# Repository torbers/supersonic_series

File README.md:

# Supersonic Series

Airplane dragon synthesizers

## Spike chord synthesizer
### Instruction card

### MIDI CC implementation
| Controller | Effect |
| --- | --- |
| 70 | Chord shape |
| 71 | Filter resonance |
| 72 | Amp envelope attack |
| 73 | Amp envelope release |
| 74 | Filter frequency |
| 75 | Delay time |
| 76 | Delay feedback |
| 77 | Detune |
| 78 | Oscillator bank spread |

### Building Arduino code
The Arduino IDE is the easiest, most portable way to compile and upload code to Spike. This section assumes no previous knowledge of the Arduino IDE in order to accommodate coders of all experience levels.
#### 1. Install Arduino IDE
Follow [this tutorial](https://docs.arduino.cc/software/ide-v2/tutorials/getting-started/ide-v2-downloading-and-installing/) to install the Arduino IDE 2 on your computer. The environment supports Windows, Mac, and Linux.

#### 2. Clone this repository
Use your preferred method to "clone" (download) this repository to your computer. I like the [github desktop app](https://desktop.github.com/download/), but you can also just download the whole thing as a .zip from the [main page](https://github.com/torbers/supersonic_series).

#### 3. Open the file
Once the IDE has installed, choose `File->Open` and navigate to and open `supersonic_series/spike copy/spike_v2_usb/spike_v2_usb.ino`. **Make sure** `spike_v2_usb.ino` and the other files stay in the `spike_v2_usb` folder or it won't open correctly!

#### 4. Install libraries
You will need to install 3 libraries from the built-in library manager (the book icon on the side of the Arduino window).
- **Mozzi** by Tim Barrass: This is our sound synthesis library
- **USB-MIDI** by lathoub: This library sends and recieves MIDI over USB
- **Adafruit_NeoPixel** by Adafruit: This library controls the built in LED

#### 5. Connect Spike
Connect Spike to your computer via the USB C port. **Make sure your cable is capable of data transmission or "sync," and isn't a power-only cable.**
It will appear in Arduino as `Arduino Zero (Native USB)` at the top of the screen. Make sure the text saying this is bold - if so, you're ready to upload.

#### 6. Compile and upload!
Press the arrow button at the top left of the screen to compile and upload the code.

---
## Licensing
All work is shared under [Creative Commons CC BY-SA 4.0](https://creativecommons.org/licenses/by-sa/4.0/): Anyone is free to share, remix, and commercialize it so long as they attribute the work and release it under this same license agreement. (Attribution text modified from [here](https://fullyautomatedrpg.com/licensing/).)

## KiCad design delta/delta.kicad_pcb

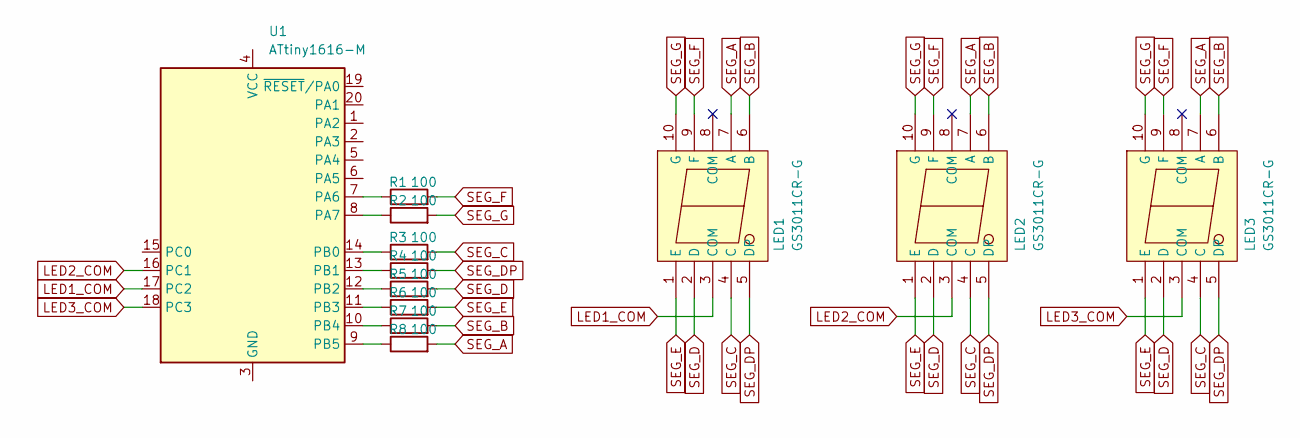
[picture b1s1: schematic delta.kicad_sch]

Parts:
LED1, LED2, LED3: GS3011CR-G; LED-SEG-SMD_10P-L12.0-W7.3-P1.50-BL; MPN GS3011CR-G; LCSC Part C22462656
R1, R2, R3, R4, R5, R6, R7, R8: 100; R_0402_1005Metric
U1: ATtiny1616-M; VQFN-20-1EP_3x3mm_P0.4mm_EP1.7x1.7mm

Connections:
LED1_COM: LED1.3 (COM), U1.17 (PC2)
LED2_COM: LED2.3 (COM), U1.16 (PC1)
LED3_COM: LED3.3 (COM), U1.18 (PC3)
unnamed: U1.3 (GND), U1.21 (GND)
unnamed: R1.1, U1.7 (PA6)
unnamed: R2.1, U1.8 (PA7)
unnamed: R3.1, U1.14 (PB0)
unnamed: R4.1, U1.13 (PB1)
unnamed: R5.1, U1.12 (PB2)
unnamed: R6.1, U1.11 (PB3)
unnamed: R7.1, U1.10 (PB4)
unnamed: R8.1, U1.9 (PB5)
SEG_A: LED1.7 (A), LED2.7 (A), LED3.7 (A), R8.2
SEG_B: LED1.6 (B), LED2.6 (B), LED3.6 (B), R7.2
SEG_C: LED1.4 (C), LED2.4 (C), LED3.4 (C), R3.2
SEG_D: LED1.2 (D), LED2.2 (D), LED3.2 (D), R5.2
SEG_DP: LED1.5 (DP), LED2.5 (DP), LED3.5 (DP), R4.2
SEG_E: LED1.1 (E), LED2.1 (E), LED3.1 (E), R6.2
SEG_F: LED1.9 (F), LED2.9 (F), LED3.9 (F), R1.2
SEG_G: LED1.10 (G), LED2.10 (G), LED3.10 (G), R2.2

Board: 4 copper layers, 12 parts (9 on the bottom side), 20 nets, no tracks yet.

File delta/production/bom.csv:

Designator,Footprint,Quantity,Value,LCSC Part #
"LED1, LED2, LED3",LED-SEG-SMD_10P-L12.0-W7.3-P1.50-BL,3,GS3011CR-G,C22462656
U1,VQFN-20-1EP_3x3mm_P0.4mm_EP1.7x1.7mm,1,ATtiny1616-M,

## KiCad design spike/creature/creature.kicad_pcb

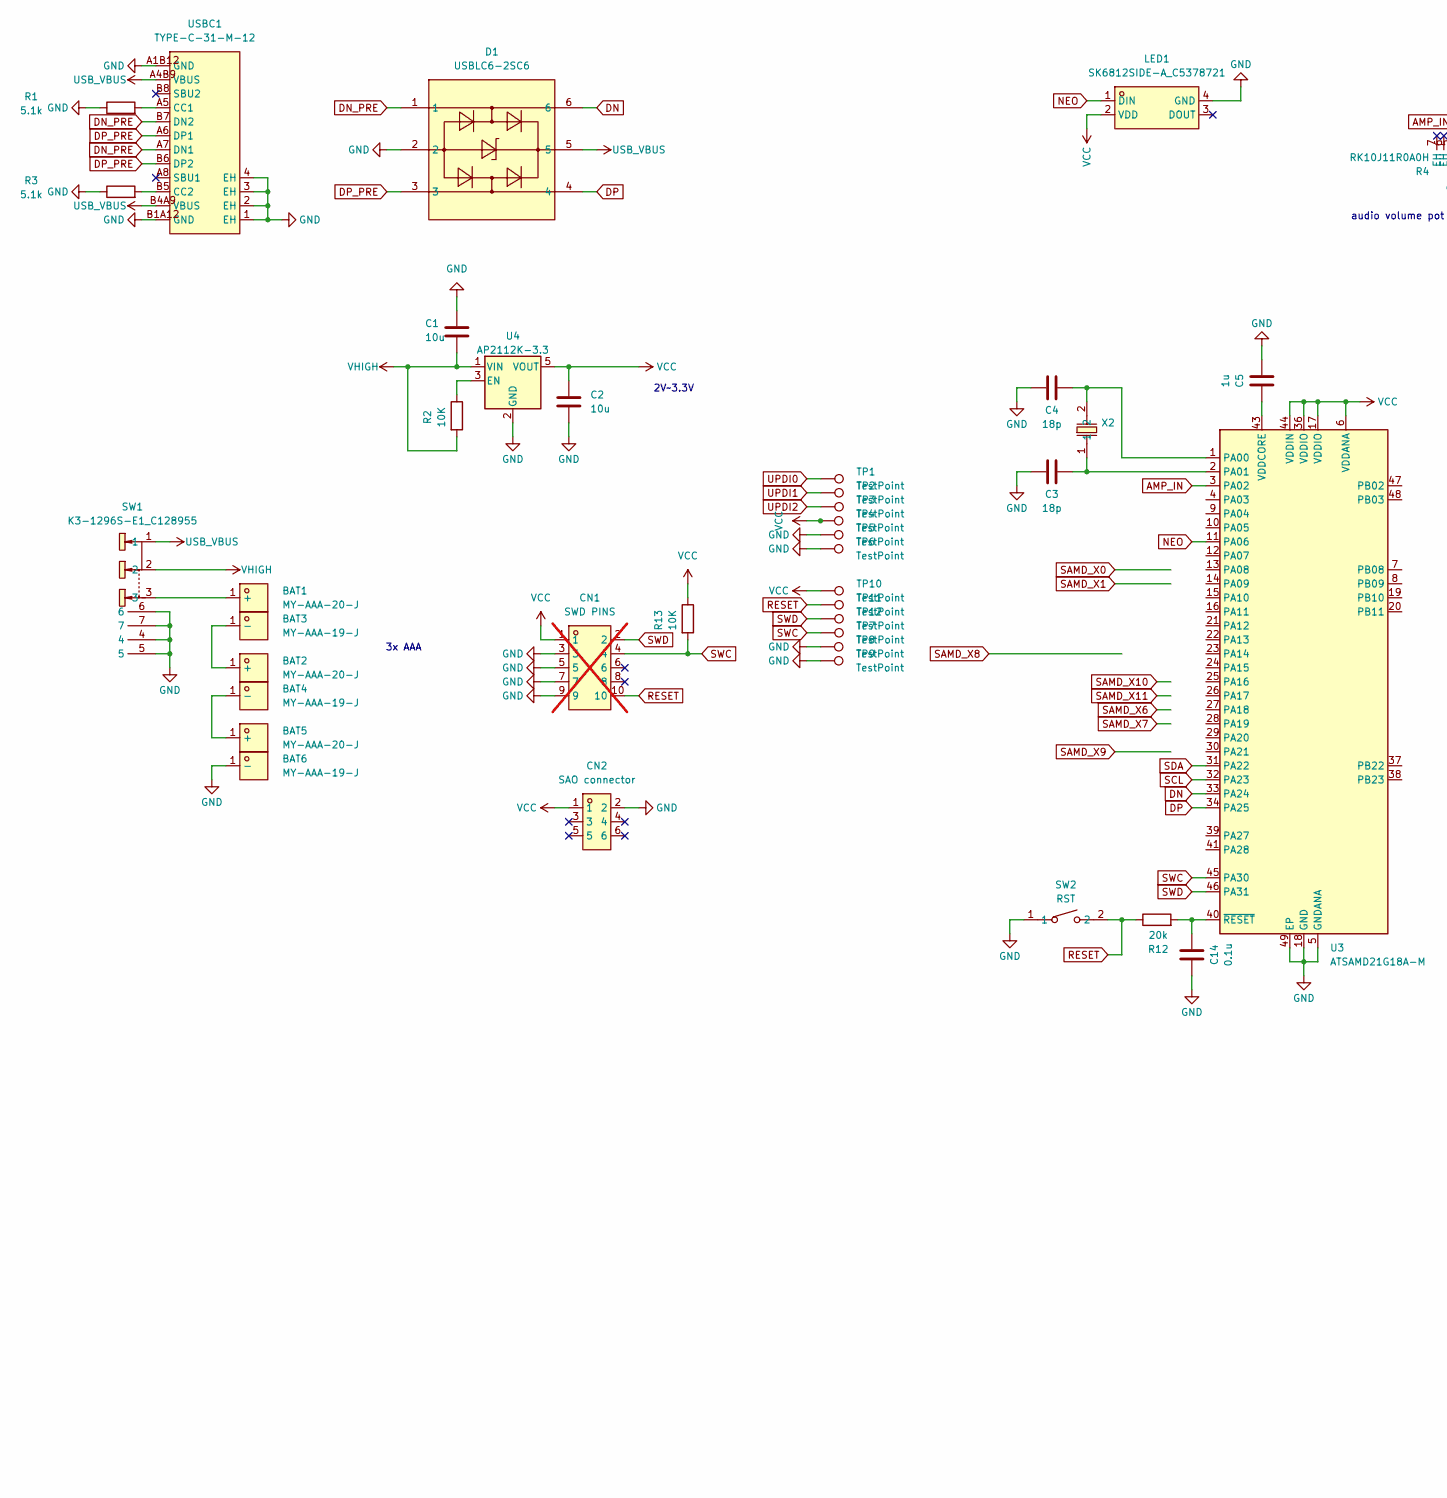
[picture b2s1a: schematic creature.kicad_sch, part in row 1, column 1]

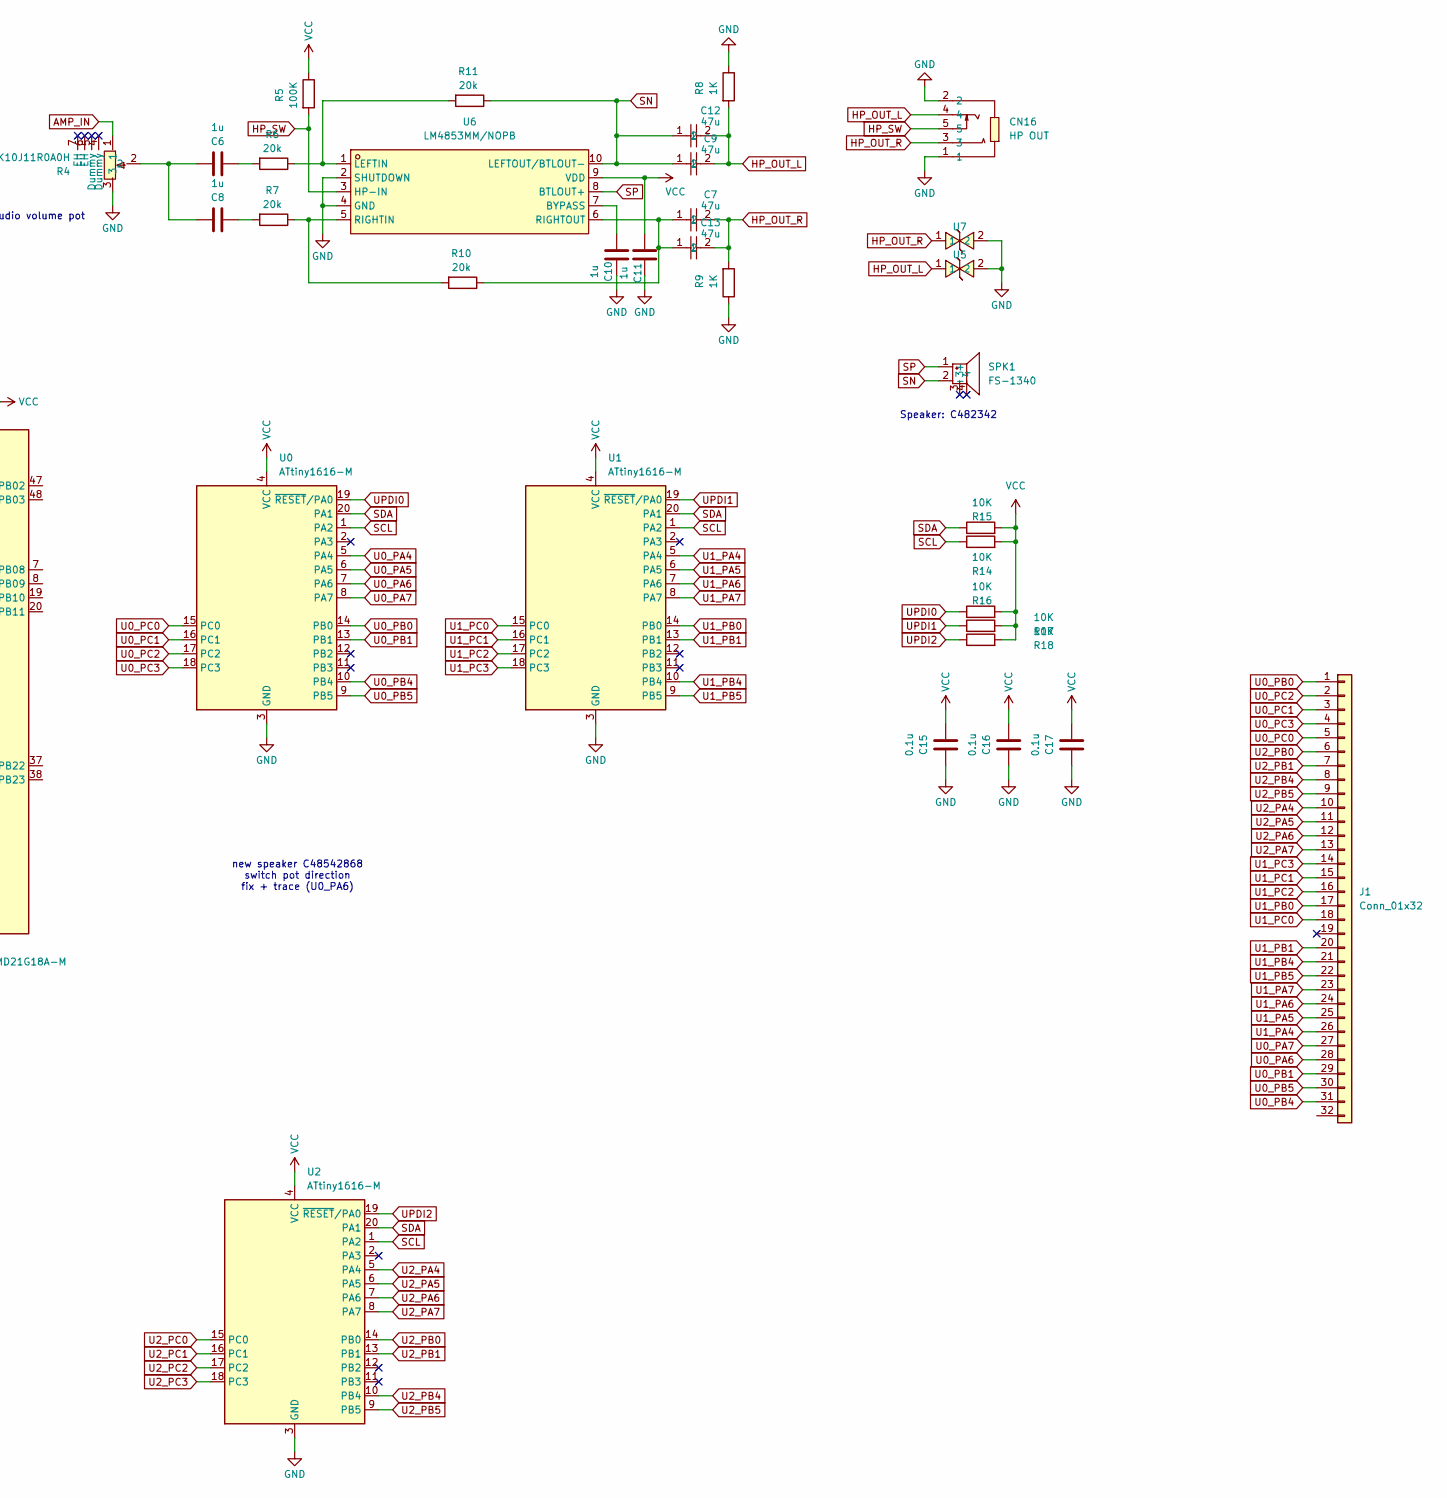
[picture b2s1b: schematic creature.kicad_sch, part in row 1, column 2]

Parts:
BAT1, BAT2, BAT5: MY-AAA-20-J; BAT-SMD_MY-AAA-20-J; MPN MY-AAA-20-J; LCSC Part C6937107
BAT3, BAT4, BAT6: MY-AAA-19-J; BAT-SMD_MY-AAA-19-J; MPN MY-AAA-19-J; LCSC Part C6937104
C1, C2: 10u; C_0402_1005Metric
C3, C4: 18p; C_0402_1005Metric
C5, C6, C8, C10, C11: 1u; C_0402_1005Metric
C7, C9, C12, C13: 47u; C0805; MPN CL21A476MQYNNNE; LCSC Part C16780
C14, C15, C16, C17: 0.1u; C_0402_1005Metric
CN1: SWD PINS; IDC-SMD_10P-P1.27-3220-10-0300-00; MPN HX JN1.27-2x5 TP H4.9; LCSC Part C42372555; not fitted
CN2: SAO connector; CONN-SMD_6P-P2.54_BH254VS; MPN BH254VS-6P; LCSC Part C492445
CN16: HP OUT; AUDIO-SMD_PJ-327A5JJ; LCSC Part C668605
D1: USBLC6-2SC6; SOT-23-6_L2.9-W1.6-P0.95-LS2.8-BL; LCSC Part C7519
J1: Conn_01x32; spike_copper
LED1: SK6812SIDE-A_C5378721; LED-SMD_4P-L4.0-W1.6-L; LCSC Part C5378721
R1, R3: 5.1k; R_0402_1005Metric
R2, R13, R14, R15, R16, R17, R18: 10K; R_0402_1005Metric
R4: RK10J11R0A0H; RES-SMD_RK10J11R0A0H; MPN RK10J11R0A0H; LCSC Part C470766
R5: 100K; R_0402_1005Metric
R6, R7, R10, R11, R12: 20k; R_0402_1005Metric
R8, R9: 1K; R_0402_1005Metric
SPK1: FS-1340; BUZ-SMD_4P-L13.0-W13.0-P11.4-BL; MPN FS-1340; LCSC Part C482342
SW1: K3-1296S-E1_C128955; SW-TH_K3-1296S-E1; MPN K3-1296S-E1; LCSC Part C128955
SW2: RST; SW-SMD_L3.9-W3.0-P4.45; LCSC Part C720477
TP1, TP2, TP3, TP4, TP5, TP6, TP7, TP8, TP9, TP10, TP11, TP12: TestPoint; TestPoint_Pad_1.5x1.5mm
U0, U1, U2: ATtiny1616-M; VQFN-20-1EP_3x3mm_P0.4mm_EP1.7x1.7mm
U3: ATSAMD21G18A-M; QFN-48-1EP_7x7mm_P0.5mm_EP5.15x5.15mm
U4: AP2112K-3.3; SOT-23-5
U5, U7: H3V3U10B; DFN1006-2L-BI; LCSC Part C20615782
U6: LM4853MM/NOPB; MSOP-10_L3.0-W3.0-P0.50-LS4.9-BL; MPN LM4853MM/NOPB; LCSC Part C2872995
USBC1: TYPE-C-31-M-12; USB-C_SMD-TYPE-C-31-M-12_1; LCSC Part C165948
X2: Q13FC1350000400; FC-135R_L3.2-W1.5; MPN Q13FC13500004; LCSC Part C32346

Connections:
AMP_IN: R4.1, U3.3 (PA02)
DN: D1.6, U3.33 (PA24)
DN_PRE: D1.1, USBC1.A7 (DN1), USBC1.B7 (DN2)
DP: D1.4, U3.34 (PA25)
DP_PRE: D1.3, USBC1.A6 (DP1), USBC1.B6 (DP2)
GND: BAT6.1 (-_1), C1.2, C2.2, C3.1, C4.1, C5.1, C10.2, C11.2, C14.1, C15.2, C16.2, C17.2, CN1.3, CN1.5, CN1.7, CN1.9, CN2.2, CN16.1, CN16.2, D1.2, LED1.4 (GND), R1.1, R3.1, R4.3, R8.1, R9.1, SW1.4, SW1.5, SW1.6, SW1.7, SW2.1, TP5.1 (1_1), TP6.1 (1_1), TP8.1 (1_1), TP9.1 (1_1), U0.3 (GND), U0.21 (GND), U1.3 (GND), U1.21 (GND), U2.3 (GND), U2.21 (GND), U3.5 (GNDANA), U3.18 (GND), U3.35 (GND), U3.42 (GND), U3.49 (EP), U4.2 (GND), U5.2, U6.2 (SHUTDOWN), U6.4 (GND), U7.2, USBC1.1 (EH), USBC1.2 (EH), USBC1.3 (EH), USBC1.4 (EH), USBC1.A1B12 (GND), USBC1.B1A12 (GND)
HP_OUT_L: C9.2, C12.2, CN16.4, R8.2, U5.1
HP_OUT_R: C7.2, C13.2, CN16.3, R9.2, U7.1
HP_SW: CN16.5, R5.2, U6.3 (HP-IN)
NEO: LED1.1 (DIN), U3.11 (PA06)
unnamed: BAT1.1 (+_1), SW1.3
unnamed: BAT2.1 (+_1), BAT3.1 (-_1)
unnamed: BAT4.1 (-_1), BAT5.1 (+_1)
unnamed: C6.1, R6.2
unnamed: C6.2, C8.2, R4.2
unnamed: C8.1, R7.2
unnamed: C4.2, U3.1 (PA00), X2.2
unnamed: C3.2, U3.2 (PA01), X2.1
unnamed: C5.2, U3.43 (VDDCORE)
unnamed: C14.2, R12.2, U3.40 (~RESET)
unnamed: R2.1, U4.3 (EN)
unnamed: C10.1, U6.7 (BYPASS)
unnamed: R6.1, R11.2, U6.1 (LEFTIN)
unnamed: R7.1, R10.2, U6.5 (RIGHTIN)
unnamed: C7.1, C13.1, R10.1, U6.6 (RIGHTOUT)
unnamed: R1.2, USBC1.A5 (CC1)
unnamed: R3.2, USBC1.B5 (CC2)
RESET: CN1.10, R12.1, SW2.2, TP11.1 (1_1)
SCL: R14.1, U0.1 (PA2), U1.1 (PA2), U2.1 (PA2), U3.32 (PA23)
SDA: R15.1, U0.20 (PA1), U1.20 (PA1), U2.20 (PA1), U3.31 (PA22)
SN: C9.1, C12.1, R11.1, SPK1.2 (-), U6.10 (LEFTOUT/BTLOUT-)
SP: SPK1.1 (+), U6.8 (BTLOUT+)
SWC: CN1.4, R13.2, TP7.1 (1_1), U3.45 (PA30)
SWD: CN1.2, TP12.1 (1_1), U3.46 (PA31)
U0_PA4: U0.5 (PA4)
U0_PA5: U0.6 (PA5)
U0_PA6: J1.28, U0.7 (PA6)
U0_PA7: J1.27, U0.8 (PA7)
U0_PB0: J1.1, U0.14 (PB0)
U0_PB1: J1.29, U0.13 (PB1)
U0_PB4: J1.31, U0.10 (PB4)
U0_PB5: J1.30, U0.9 (PB5)
U0_PC0: J1.5, U0.15 (PC0)
U0_PC1: J1.3, U0.16 (PC1)
U0_PC2: J1.2, U0.17 (PC2)
U0_PC3: J1.4, U0.18 (PC3)
U1_PA4: J1.26, U1.5 (PA4)
U1_PA5: J1.25, U1.6 (PA5)
U1_PA6: J1.24, U1.7 (PA6)
U1_PA7: J1.23, U1.8 (PA7)
U1_PB0: J1.17, U1.14 (PB0)
U1_PB1: J1.20, U1.13 (PB1)
U1_PB4: J1.21, U1.10 (PB4)
U1_PB5: J1.22, U1.9 (PB5)
U1_PC0: J1.18, U1.15 (PC0)
U1_PC1: J1.15, U1.16 (PC1)
U1_PC2: J1.16, U1.17 (PC2)
U1_PC3: J1.14, U1.18 (PC3)
U2_PA4: J1.10, U2.5 (PA4)
U2_PA5: J1.11, U2.6 (PA5)
U2_PA6: J1.12, U2.7 (PA6)
U2_PA7: J1.13, U2.8 (PA7)
U2_PB0: J1.6, U2.14 (PB0)
U2_PB1: J1.7, U2.13 (PB1)
U2_PB4: J1.8, U2.10 (PB4)
U2_PB5: J1.9, U2.9 (PB5)
U2_PC0: U2.15 (PC0)
U2_PC1: U2.16 (PC1)
U2_PC2: U2.17 (PC2)
U2_PC3: U2.18 (PC3)
UPDI0: R16.1, TP1.1 (1_1), U0.19 (~RESET/PA0)
UPDI1: R17.1, TP2.1 (1_1), U1.19 (~RESET/PA0)
UPDI2: R18.1, TP3.1 (1_1), U2.19 (~RESET/PA0)
USB_VBUS: D1.5, SW1.1, USBC1.A4B9 (VBUS), USBC1.B4A9 (VBUS)
VCC: C2.1, C11.1, C15.1, C16.1, C17.1, CN1.1, CN2.1, LED1.2 (VDD), R5.1, R13.1, R14.2, R15.2, R16.2, R17.2, R18.2, TP4.1 (1_1), TP10.1 (1_1), U0.4 (VCC), U1.4 (VCC), U2.4 (VCC), U3.6 (VDDANA), U3.17 (VDDIO), U3.36 (VDDIO), U3.44 (VDDIN), U4.5 (VOUT), U6.9 (VDD)
VHIGH: C1.1, R2.2, SW1.2, U4.1 (VIN)

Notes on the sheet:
3x AAA
new speaker C48542868 switch pot direction fix + trace (U0_PA6)
audio volume pot
Speaker: C482342
2V~3.3V

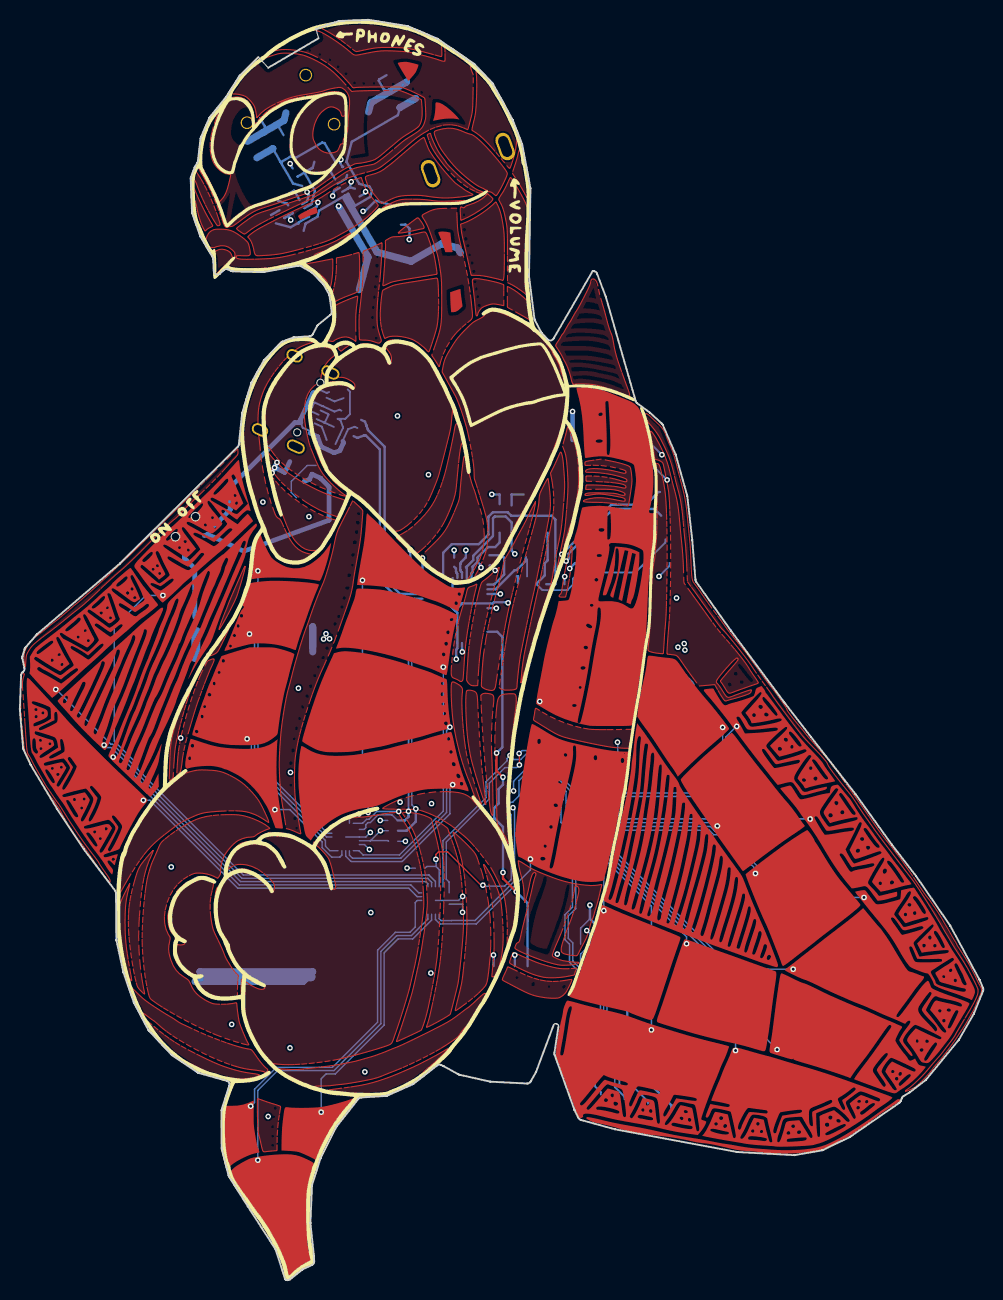
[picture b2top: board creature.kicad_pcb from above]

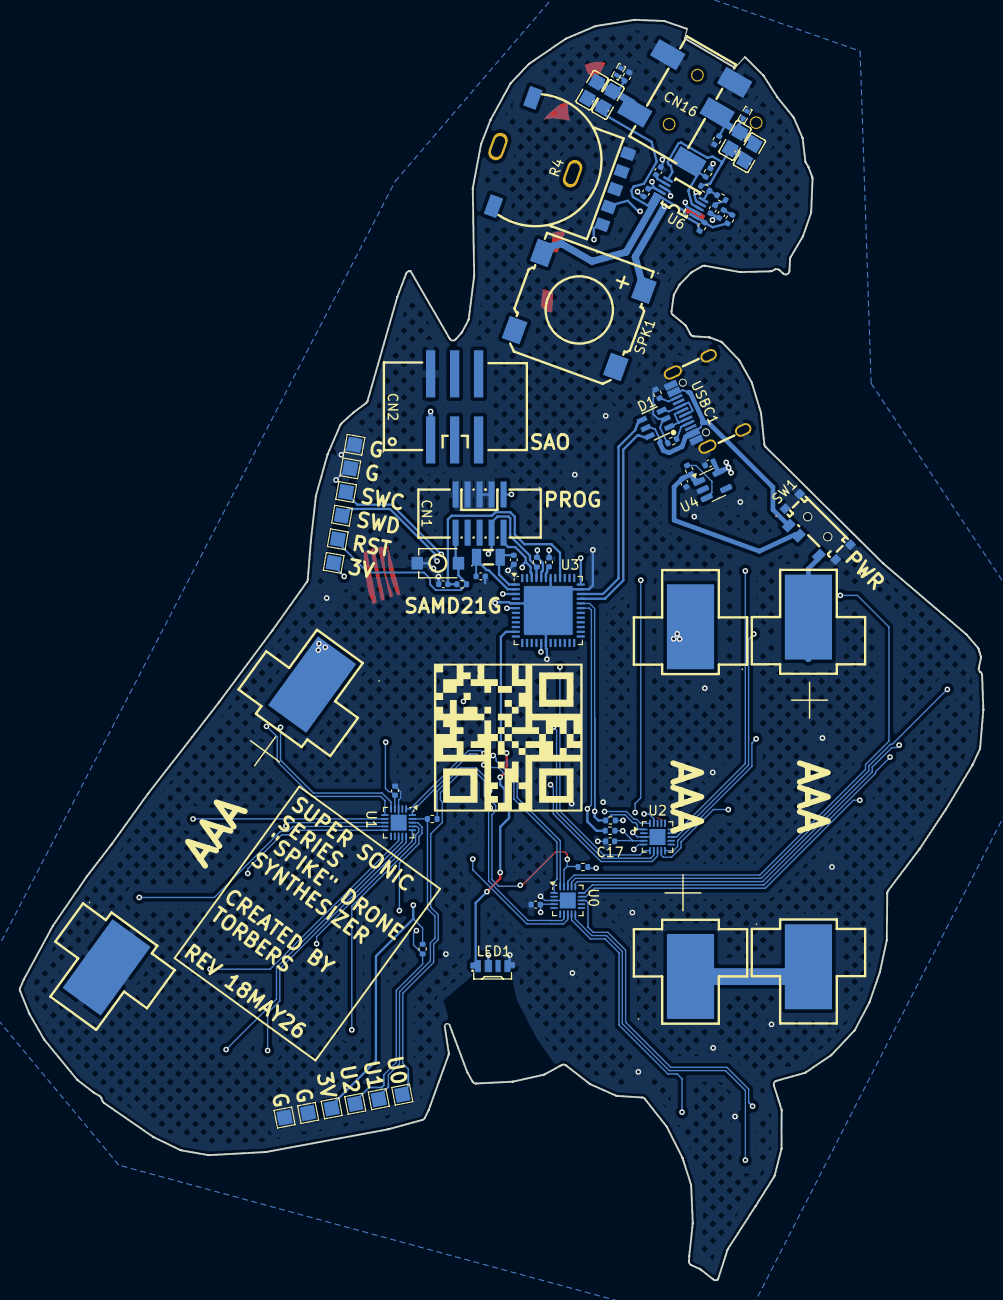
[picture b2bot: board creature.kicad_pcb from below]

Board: 4 copper layers, 102.0 x 133.4 mm, 72 parts (71 on the bottom side), 70 nets.

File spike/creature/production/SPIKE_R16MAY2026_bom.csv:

Designator,Footprint,Quantity,Value,LCSC Part #
,,1,,
"BAT1, BAT2, BAT5",BAT-SMD_MY-AAA-20-J,3,MY-AAA-20-J,C6937107
"BAT3, BAT4, BAT6",BAT-SMD_MY-AAA-19-J,3,MY-AAA-19-J,C6937104
"C1, C2",0402,2,10u,
"C10, C11, C5, C6, C8",0402,5,1u,
"C12, C13, C7, C9",C0805,4,47u,C16780
"C14, C15, C16, C17",0402,4,0.1u,
"C3, C4",0402,2,18p,
CN1,IDC-SMD_10P-P1.27-3220-10-0300-00,1,SWD PINS,C42372555
CN16,AUDIO-SMD_PJ-327A5JJ,1,HP OUT,C668605
CN2,CONN-SMD_6P-P2.54_BH254VS,1,SAO connector,C492445
D1,SOT-23-6_L2.9-W1.6-P0.95-LS2.8-BL,1,USBLC6-2SC6,C7519
J1,spike_copper,1,Conn_01x32,
LED1,LED-SMD_4P-L4.0-W1.6-L,1,SK6812SIDE-A_C5378721,C5378721
"R1, R3",0402,2,5.1k,
"R10, R11, R12, R6, R7",0402,5,20k,
"R13, R14, R15, R16, R17, R18, R2",0402,7,10K,
R4,RES-SMD_RK10J11R0A0H,1,RK10J11R0A0H,C470766
R5,0402,1,100K,
"R8, R9",0402,2,1K,
SPK1,BUZ-SMD_4P-L13.0-W13.0-P11.4-BL,1,FS-1340,C482342
SW1,SW-TH_K3-1296S-E1,1,K3-1296S-E1_C128955,C128955
SW2,SW-SMD_L3.9-W3.0-P4.45,1,RST,C720477
"TP1, TP10, TP11, TP12, TP2, TP3, TP4, TP5, TP6, TP7, TP8, TP9",TestPoint_Pad_1.5x1.5mm,12,TestPoint,
"U0, U1, U3",VQFN-20-1EP_3x3mm_P0.4mm_EP1.7x1.7mm,3,ATtiny1616-M,
U2,QFN-48-1EP_7x7mm_P0.5mm_EP5.15x5.15mm,1,ATSAMD21G18A-M,
U4,SOT-23-5,1,AP2112K-3.3,
"U5, U7",DFN1006-2L-BI,2,H3V3U10B,C20615782
U6,MSOP-10_L3.0-W3.0-P0.50-LS4.9-BL,1,LM4853MM/NOPB,C2872995
USBC1,USB-C_SMD-TYPE-C-31-M-12_1,1,TYPE-C-31-M-12,C165948
X2,FC-135R_L3.2-W1.5,1,Q13FC1350000400,C32346

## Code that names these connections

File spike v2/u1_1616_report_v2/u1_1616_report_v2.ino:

#include "Slider.h"

#define NODE_COUNT 12
Slider slider1;

uint8_t sensors_pins[NODE_COUNT] = {PIN_PC3, PIN_PC2, PIN_PC1, PIN_PC0, PIN_PB0, PIN_PB1, PIN_PB5, PIN_PB4, PIN_PA6, PIN_PA7, PIN_PA5, PIN_PA4};
volatile int16_t iv[12];

int16_t max_vals[NODE_COUNT] = {512, 110, 510, 402, 336, 292, 508, 508, 512, 500, 68, 512};

uint8_t cal_max[NODE_COUNT];


void setup() {
  slider1.begin(sensors_pins);
  delay(100);

  slider1.update();
  delay(100);

  for (uint8_t i = 0; i < NODE_COUNT; i++){
    //ptc_node_set_gain(&slider1.s_nodes[i], 1, 1); 
    //delay(100);
  }

  /*
  ptc_node_set_gain(&slider1.s_nodes[0], 1, 1); 
  ptc_node_set_gain(&slider1.s_nodes[1], 1, 1); 
  ptc_node_set_gain(&slider1.s_nodes[2], 1, 1); 
  ptc_node_set_gain(&slider1.s_nodes[3], 1, 1); 
  */

  // put your setup code here, to run once:
  //Wire.pins(PIN_PB1, PIN_PB0);
  Wire.pins(PIN_PA1, PIN_PA2);
  
  Wire.begin(0x61);
  Wire.onRequest(requestHandler);
}

void loop() {
  // put your main code here, to run repeatedly:
  ptc_process(millis());
  slider1.update();
  slider1.capTouchCurrent[0] -= 504;

  for (uint8_t p = 0; p < 12; p++){
    iv[p] = slider1.capTouchCurrent[p];
    cal_max[p] = (uint8_t) constrain((float(iv[p]) / float(max_vals[p]) * 255), 0, 255);
    //iv[p] = slider1.capTouchRead(p);
  }

}

void requestHandler() {
  for (uint8_t r = 0; r < 12; r++){
    //Wire.write(values[r]);
    //Wire.write((uint8_t) (iv[r] >> 8) & 0xFF);
    //Wire.write((uint8_t) (iv[r]) & 0xFF);
    Wire.write(cal_max[r]);
  }
}



void ptc_event_callback(const ptc_cb_event_t eventType, cap_sensor_t* node) {
  #ifdef DEBUG_SERIAL
  if (PTC_CB_EVENT_TOUCH_DETECT == eventType) {
    Serial.print("node touched:");
    Serial.println(ptc_get_node_id(node));
  } else if (PTC_CB_EVENT_TOUCH_RELEASE == eventType) {
    Serial.print("node released:");
    Serial.println(ptc_get_node_id(node));
  } else if (PTC_CB_EVENT_CONV_MUTUAL_CMPL == eventType) {
    // Do more complex things here
  } else if (PTC_CB_EVENT_CONV_CALIB & eventType) {
    if (PTC_CB_EVENT_ERR_CALIB_LOW == eventType) {
      Serial.print("Calib error, Cc too low.");
    } else if (PTC_CB_EVENT_ERR_CALIB_HIGH == eventType) {
      Serial.print("Calib error, Cc too high.");
    } else if (PTC_CB_EVENT_ERR_CALIB_TO == eventType) {
      Serial.print("Calib error, calculation timeout.");
    } else {
      Serial.print("Calib Successful.");
    }
    Serial.print(" Node: ");
    Serial.println(ptc_get_node_id(node));
  }
  #endif
}

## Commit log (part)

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2026-05-20 spike
2026-05-20 name
2026-06-05 madde
2026-06-16 many
2026-06-29 first release
